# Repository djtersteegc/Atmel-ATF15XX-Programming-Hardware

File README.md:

Recently I needed to program some Atmel ATF1504AS and ATF1508AS CPLD's as part of Peter Schranz's [RVL12 emulator](https://www.5volts.ch/pages/rlv12v2/) project.  I had worked with similar Altera Max 7000 EPM7128SLC84 CPLD's that can be programmed with the readily available USB Blaster clones (~$20), but the only modern'ish programmer available for the Atmel's was Kana/Microchip's [ATDH1150USB](https://www.microchip.com/en-us/development-tool/atdh1150usb) which has risen to ~$100 over the last few years and seems to be getting harder to find in stock.  I tried various other FTDI based programmers and OpenOCD using the excellent writeup on https://www.hackup.net/2020/01/erasing-and-programming-the-atf1504-cpld/, but I couldn't get that setup to work reliably(3.3V source with 5V target?) so I ended up buying an uncased ATDH1150USB off eBay (unfortunately shipping from England to the US was more than the programmer itself), which worked great but got me motivated to do some additional work in this area.

# [ATDH1150USB 3D Printed Case](Atmel-ATDH1150USB-Case)

First I needed a case.  Simple two piece model that screws together with two M3x10mm taper head screws.

# [Atmel-ATF15XX-Programming-Adapter](Atmel-ATF15XX-Programming-Adapter)

Next I wanted to create a programming adapter than takes either a PLCC44 or PLCC84 adapter board to allow for easy used chip testing and programming. I had bought some cheap ATF1508AS's from AliExpress and a couple of them were JTAG locked so I needed a way to apply 12V to the OE1 pin to restore JTAG functionality. I had designed a similar board for [Xilinx XC9500](https://github.com/djtersteegc/xilinx-xc9500xl-programming-adapter) CPLD's, so this was a variation on that theme.

[Atmel-ATF15XX-Programming-Adapter Schematic](https://djtersteegc.github.io/Atmel-ATF15XX-Programming-Hardware/Atmel-ATF15XX-Programming-Adapter-Schematic-v1.0.pdf)

[Atmel-ATF15XX-Programming-Adapter BOM](https://djtersteegc.github.io/Atmel-ATF15XX-Programming-Hardware/Atmel-ATF15XX-Programming-Adapter-ibom-v1.0.html)

JP1 selected whetherthe ATF15xx will be powered by the (optional) onboard VRM's or directly from the supply into the DC barrel jack.

JP2 selects whether you'll see 5V or 3.3V volts at the ATF15xx.  When using the VRM's, make sure the supply voltage is a couple of volts higher, but less than the 12V being output by the boost convertor.

The bottom left locking push button controls board power, and the top right controls if +12V is routed to OE1 on the ATF15xx. When needing to execute this to reenable JTAG, make sure to apply VCC first, then 12V (top right button), program the chip, power off 12V, and then power off VCC. You may initially get a verify error on this program attempt, but once you repower the chip and try again, everything should work normally.

I designed three adapter PCB's for both normal PLCC sockets and a PLCC84 test socket.  

[PLCC-44-Socket-Adapter](PLCC-44-Socket-Adapter)	[Schematic](https://djtersteegc.github.io/Atmel-ATF15XX-Programming-Hardware/PLCC-44-Socket-Adapter-Schematic-v1.0.pdf)	[BOM](https://djtersteegc.github.io/Atmel-ATF15XX-Programming-Hardware/PLCC-44-Socket-Adapter-ibom-v1.0.html)

[PLCC-84-Socket-Adapter](PLCC-84-Socket-Adapter)	[Schematic](https://djtersteegc.github.io/Atmel-ATF15XX-Programming-Hardware/PLCC-84-Socket-Adapter-Schematic-v1.0.pdf)	[BOM](https://djtersteegc.github.io/Atmel-ATF15XX-Programming-Hardware/PLCC-84-Socket-Adapter-ibom-v1.0.html)

[PLCC-84-Test-Socket-Adapter](PLCC-84-Test-Socket-Adapter)	[Schematic](https://djtersteegc.github.io/Atmel-ATF15XX-Programming-Hardware/PLCC-84-Test-Socket-Adapter-Schematic-v1.0.pdf)	[BOM](https://djtersteegc.github.io/Atmel-ATF15XX-Programming-Hardware/PLCC-84-Test-Socket-Adapter-ibom-v1.0.html)

The PLCC84 test socket I used was this (genuine?) Yamaichi IC120-0844-303 socket without PCB that I purchased from [AliExpress](https://www.aliexpress.us/item/3256806424159192.html).  Make sure you get this model since there are other Yamaichi IC120-0844-XXX models with the "less compatible" pin pattern that won't fit.

I didn't design a PLC44 test socket to DIP44 board since these are readily available with a test socket preinstalled on [AliExpress](https://www.aliexpress.us/item/3256807303077235.html) for <$15.

Also works great for programming Max 7000's devices that share a similar pinout.

# ATMISP Compatible Programmer

I spent a bit of time reading through this [thread](https://www.forum64.de/index.php?thread/94552-atf1504as-cpld-f%C3%BCr-fe3-%C3%BCber-jtag-programmieren/) on Forum64 , and the efforts there to get various generic FTDI boards recognized by Atmel's [ATMISP](https://www.microchip.com/en-us/development-tool/atmisp) programming software.  At it's core the ATDH1150USB is an FTDI2232D with a config EEPROM to identify itself to ATMISP, level converters on the JTAG lines to support 5V and 3.3V ATF15xx chips, and some status LED's.  Here's the block diagram from the manual.

Several hours of reverse engineering and I was able to create a functional equivalent.  Went with a USB-C port since it's 2025 and dropped the JTAG-X connector to keep the board size down.

Worked great with ATMISP v7.3 on Windows 10.  Similar to the ATDH1150USB the green LED will light when connected to ATMISP, both green and red LED's when successfully executing an operation, and the red LED only when an error occurs.

Size comparison with his older brother.

I'm not going to publish the design files on this one just yet until I get rid of my initial batch of PCB's and parts, so if you are in the US and interested in an assembled and tested programmer as pictured above for half the cost of the official ATDH1150USB, drop me a line.  Should also have them up on [Tindie](https://www.tindie.com/stores/tersteeg/) in a bit.

Shield: [![CC BY-NC-SA 4.0][cc-by-nc-sa-shield]][cc-by-nc-sa]

This work is licensed under a
[Creative Commons Attribution-NonCommercial-ShareAlike 4.0 International License][cc-by-nc-sa].

[![CC BY-NC-SA 4.0][cc-by-nc-sa-image]][cc-by-nc-sa]

[cc-by-nc-sa]: http://creativecommons.org/licenses/by-nc-sa/4.0/
[cc-by-nc-sa-image]: https://licensebuttons.net/l/by-nc-sa/4.0/88x31.png
[cc-by-nc-sa-shield]: https://img.shields.io/badge/License-CC%20BY--NC--SA%204.0-lightgrey.svg

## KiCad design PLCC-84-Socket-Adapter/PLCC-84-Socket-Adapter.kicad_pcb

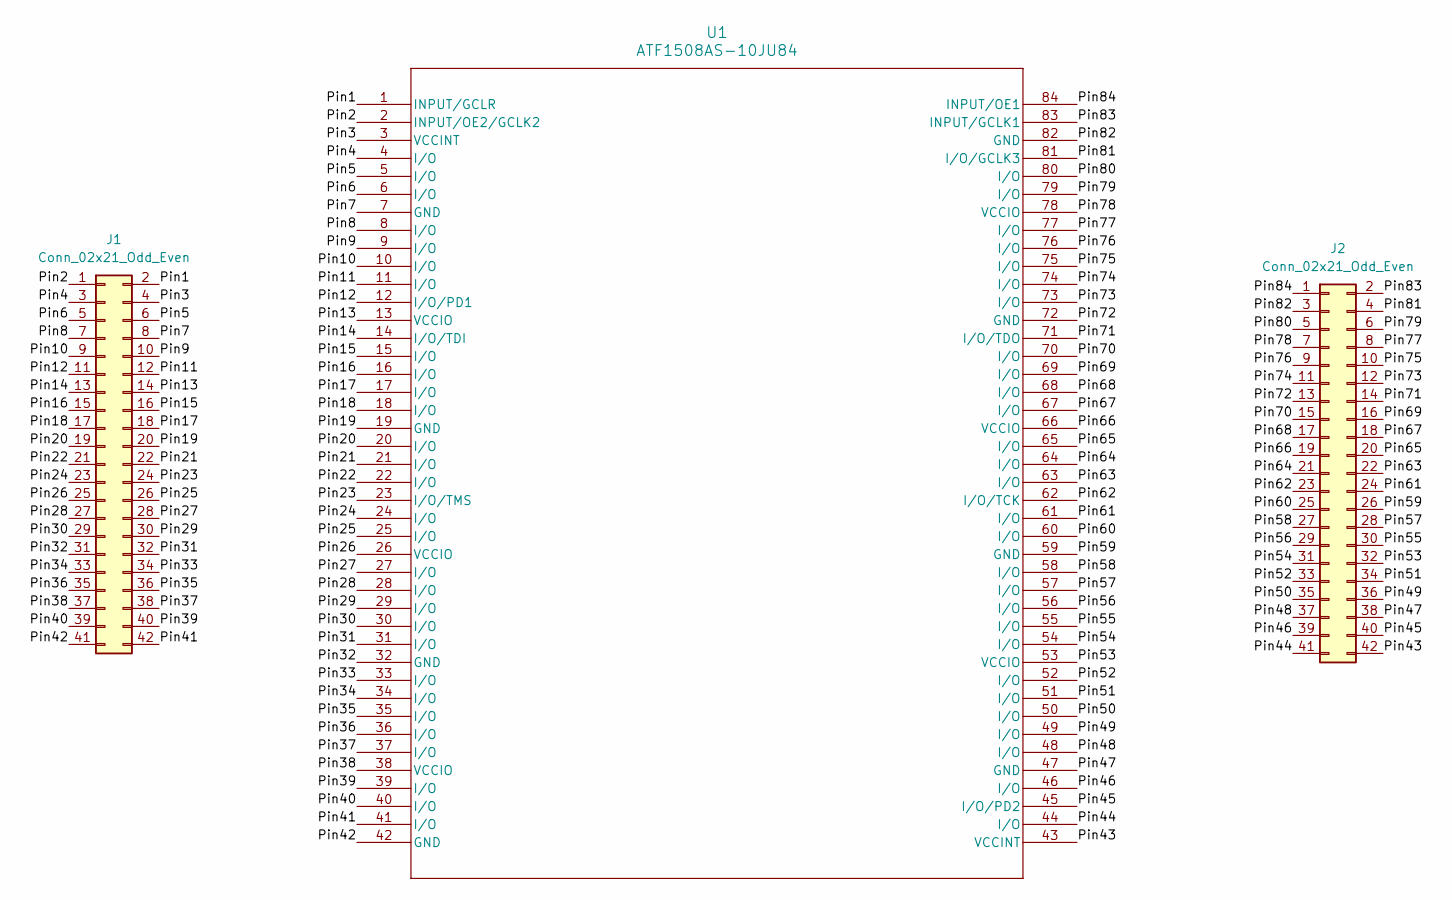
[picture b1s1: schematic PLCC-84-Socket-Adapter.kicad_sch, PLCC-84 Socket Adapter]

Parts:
J1, J2: Conn_02x21_Odd_Even; PinHeader_2x21_P2.54mm_Vertical
U1: ATF1508AS-10JU84; PLCC-84_THT-Socket

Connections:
/Pin1: J1.2, U1.1 (INPUT/GCLR)
/Pin2: J1.1, U1.2 (INPUT/OE2/GCLK2)
/Pin3: J1.4, U1.3 (VCCINT)
/Pin4: J1.3, U1.4 (I/O)
/Pin5: J1.6, U1.5 (I/O)
/Pin6: J1.5, U1.6 (I/O)
/Pin7: J1.8, U1.7 (GND)
/Pin8: J1.7, U1.8 (I/O)
/Pin9: J1.10, U1.9 (I/O)
/Pin10: J1.9, U1.10 (I/O)
/Pin11: J1.12, U1.11 (I/O)
/Pin12: J1.11, U1.12 (I/O/PD1)
/Pin13: J1.14, U1.13 (VCCIO)
/Pin14: J1.13, U1.14 (I/O/TDI)
/Pin15: J1.16, U1.15 (I/O)
/Pin16: J1.15, U1.16 (I/O)
/Pin17: J1.18, U1.17 (I/O)
/Pin18: J1.17, U1.18 (I/O)
/Pin19: J1.20, U1.19 (GND)
/Pin20: J1.19, U1.20 (I/O)
/Pin21: J1.22, U1.21 (I/O)
/Pin22: J1.21, U1.22 (I/O)
/Pin23: J1.24, U1.23 (I/O/TMS)
/Pin24: J1.23, U1.24 (I/O)
/Pin25: J1.26, U1.25 (I/O)
/Pin26: J1.25, U1.26 (VCCIO)
/Pin27: J1.28, U1.27 (I/O)
/Pin28: J1.27, U1.28 (I/O)
/Pin29: J1.30, U1.29 (I/O)
/Pin30: J1.29, U1.30 (I/O)
/Pin31: J1.32, U1.31 (I/O)
/Pin32: J1.31, U1.32 (GND)
/Pin33: J1.34, U1.33 (I/O)
/Pin34: J1.33, U1.34 (I/O)
/Pin35: J1.36, U1.35 (I/O)
/Pin36: J1.35, U1.36 (I/O)
/Pin37: J1.38, U1.37 (I/O)
/Pin38: J1.37, U1.38 (VCCIO)
/Pin39: J1.40, U1.39 (I/O)
/Pin40: J1.39, U1.40 (I/O)
/Pin41: J1.42, U1.41 (I/O)
/Pin42: J1.41, U1.42 (GND)
/Pin43: J2.42, U1.43 (VCCINT)
/Pin44: J2.41, U1.44 (I/O)
/Pin45: J2.40, U1.45 (I/O/PD2)
/Pin46: J2.39, U1.46 (I/O)
/Pin47: J2.38, U1.47 (GND)
/Pin48: J2.37, U1.48 (I/O)
/Pin49: J2.36, U1.49 (I/O)
/Pin50: J2.35, U1.50 (I/O)
/Pin51: J2.34, U1.51 (I/O)
/Pin52: J2.33, U1.52 (I/O)
/Pin53: J2.32, U1.53 (VCCIO)
/Pin54: J2.31, U1.54 (I/O)
/Pin55: J2.30, U1.55 (I/O)
/Pin56: J2.29, U1.56 (I/O)
/Pin57: J2.28, U1.57 (I/O)
/Pin58: J2.27, U1.58 (I/O)
/Pin59: J2.26, U1.59 (GND)
/Pin60: J2.25, U1.60 (I/O)
/Pin61: J2.24, U1.61 (I/O)
/Pin62: J2.23, U1.62 (I/O/TCK)
/Pin63: J2.22, U1.63 (I/O)
/Pin64: J2.21, U1.64 (I/O)
/Pin65: J2.20, U1.65 (I/O)
/Pin66: J2.19, U1.66 (VCCIO)
/Pin67: J2.18, U1.67 (I/O)
/Pin68: J2.17, U1.68 (I/O)
/Pin69: J2.16, U1.69 (I/O)
/Pin70: J2.15, U1.70 (I/O)
/Pin71: J2.14, U1.71 (I/O/TDO)
/Pin72: J2.13, U1.72 (GND)
/Pin73: J2.12, U1.73 (I/O)
/Pin74: J2.11, U1.74 (I/O)
/Pin75: J2.10, U1.75 (I/O)
/Pin76: J2.9, U1.76 (I/O)
/Pin77: J2.8, U1.77 (I/O)
/Pin78: J2.7, U1.78 (VCCIO)
/Pin79: J2.6, U1.79 (I/O)
/Pin80: J2.5, U1.80 (I/O)
/Pin81: J2.4, U1.81 (I/O/GCLK3)
/Pin82: J2.3, U1.82 (GND)
/Pin83: J2.2, U1.83 (INPUT/GCLK1)
/Pin84: J2.1, U1.84 (INPUT/OE1)

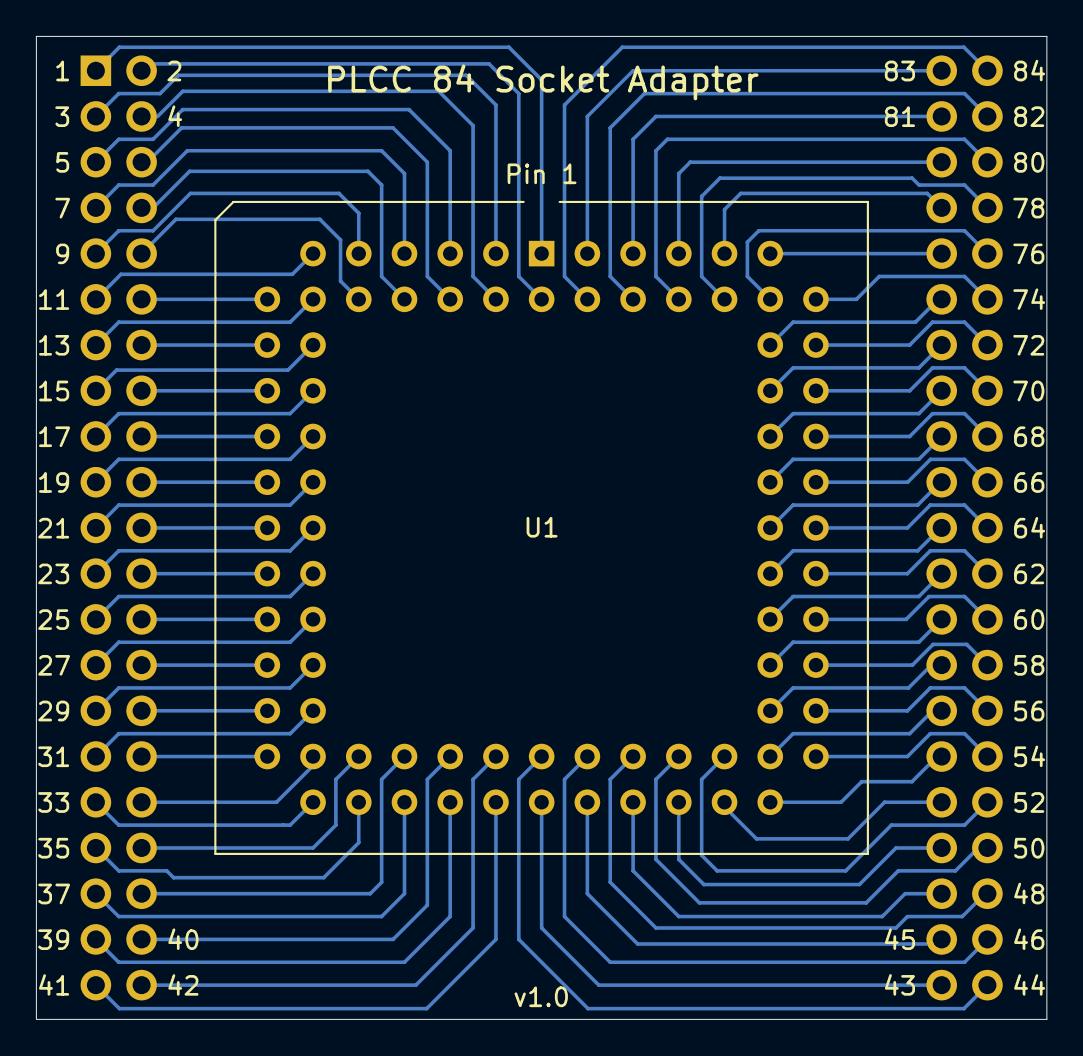
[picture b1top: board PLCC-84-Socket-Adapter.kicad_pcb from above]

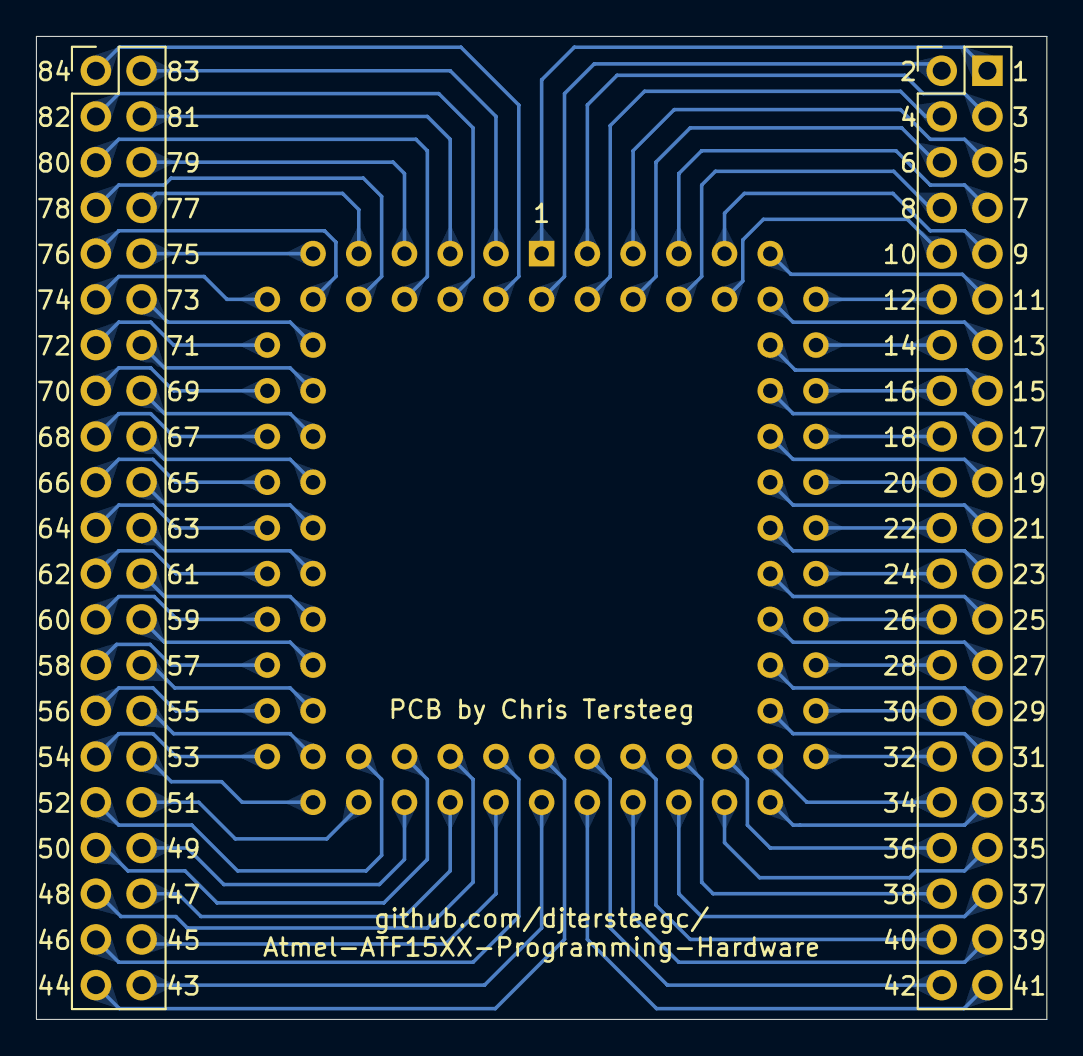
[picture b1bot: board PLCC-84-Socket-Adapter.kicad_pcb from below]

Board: 2 copper layers, 56.1 x 54.6 mm, 3 parts (2 on the bottom side), 84 nets.

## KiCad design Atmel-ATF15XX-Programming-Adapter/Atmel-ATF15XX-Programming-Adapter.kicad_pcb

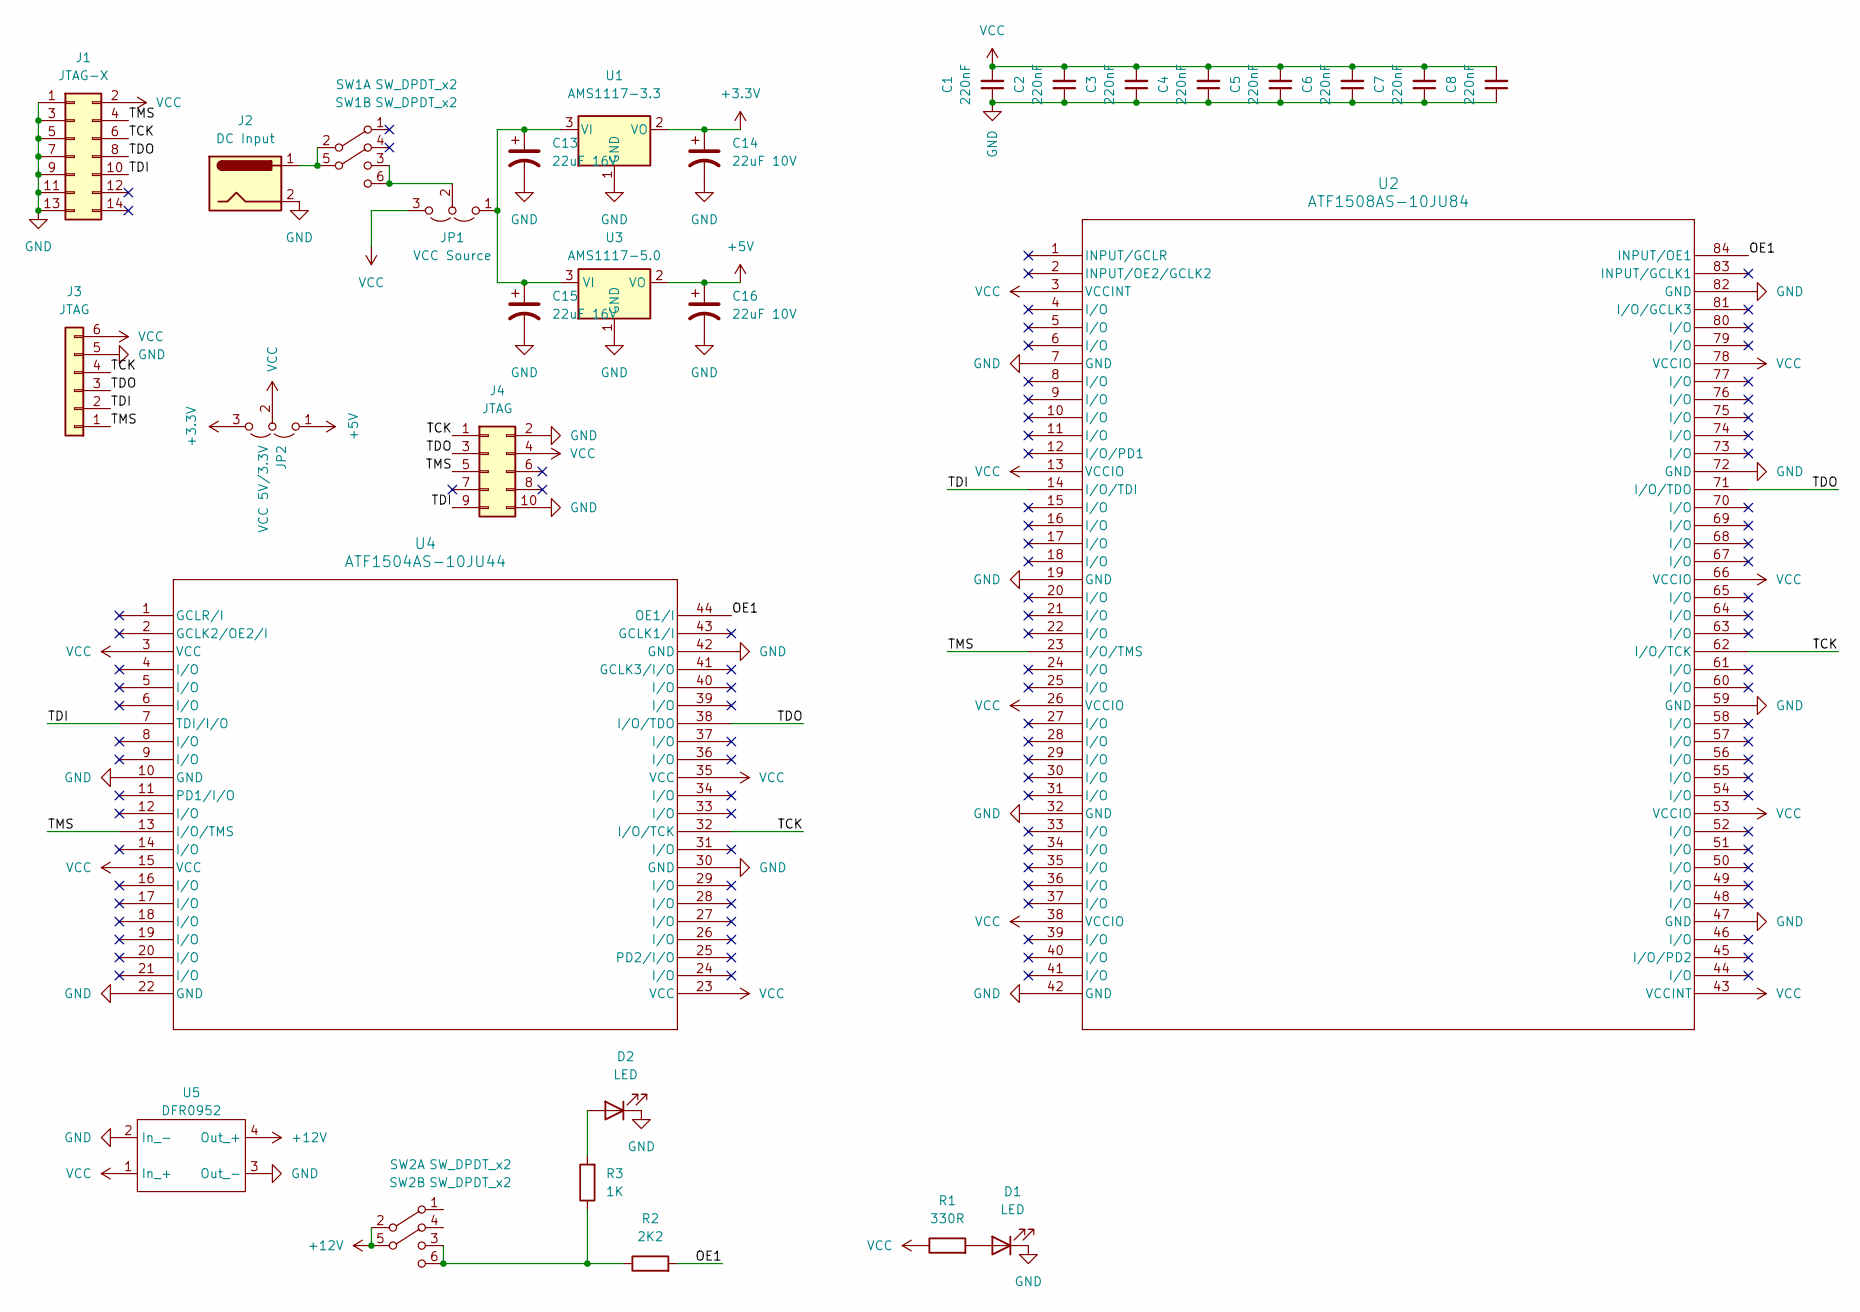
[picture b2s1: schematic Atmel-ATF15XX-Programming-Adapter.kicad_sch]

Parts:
C1, C2, C3, C4, C5, C6, C7, C8: 220nF; C_Disc_D4.7mm_W2.5mm_P5.00mm
C13, C15: 22uF 16V; CP_EIA-3528-12_Kemet-T_Pad1.50x2.35mm_HandSolder
C14, C16: 22uF 10V; CP_EIA-3528-12_Kemet-T_Pad1.50x2.35mm_HandSolder
D1, D2: LED; LED_D3.0mm
J1: JTAG-X; IDC-Header_2x07_P2.00mm_Vertical
J2: DC Input; BarrelJack_Horizontal
J3: JTAG; PinHeader_1x06_P2.54mm_Horizontal
J4: JTAG; IDC-Header_2x05_P2.54mm_Vertical
JP1: VCC Source; PinHeader_1x03_P2.54mm_Vertical
JP2: VCC 5V/3.3V; PinHeader_1x03_P2.54mm_Vertical
R1: 330R; R_Axial_DIN0207_L6.3mm_D2.5mm_P7.62mm_Horizontal
R2: 2K2; R_Axial_DIN0207_L6.3mm_D2.5mm_P7.62mm_Horizontal
R3: 1K; R_Axial_DIN0207_L6.3mm_D2.5mm_P7.62mm_Horizontal
SW1, SW2: SW_DPDT_x2; KFC8.5x8.5 DPDT Push Switch
U1: AMS1117-3.3; SOT-223-3_TabPin2
U2: ATF1508AS-10JU84; PLCC84 to Dual DIP84
U3: AMS1117-5.0; SOT-223-3_TabPin2
U4: ATF1504AS-10JU44; PLCC44-QFP44 to DIP44
U5: DFR0952; DFR0952 Mini DC-DC Boost Convertor

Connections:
+3.3V: C14.1, JP2.3 (B), U1.2 (VO)
+5V: C16.1, JP2.1 (A), U3.2 (VO)
+12V: SW2.2 (B), SW2.5 (B), U5.4 (Out_+)
/OE1: R2.2, U2.84 (INPUT/OE1), U4.44 (OE1/I)
/TCK: J1.6, J3.4, J4.1, U2.62 (I/O/TCK), U4.32 (I/O/TCK)
/TDI: J1.10, J3.2, J4.9, U2.14 (I/O/TDI), U4.7 (TDI/I/O)
/TDO: J1.8, J3.3, J4.3, U2.71 (I/O/TDO), U4.38 (I/O/TDO)
/TMS: J1.4, J3.1, J4.5, U2.23 (I/O/TMS), U4.13 (I/O/TMS)
GND: C1.1, C2.1, C3.1, C4.1, C5.1, C6.1, C7.1, C8.1, C13.2, C14.2, C15.2, C16.2, D1.1 (K), D2.1 (K), J1.1, J1.3, J1.5, J1.7, J1.9, J1.11, J1.13, J2.2, J3.5, J4.2, J4.10, U1.1 (GND), U2.7 (GND), U2.19 (GND), U2.32 (GND), U2.42 (GND), U2.47 (GND), U2.59 (GND), U2.72 (GND), U2.82 (GND), U3.1 (GND), U4.10 (GND), U4.22 (GND), U4.30 (GND), U4.42 (GND), U5.2 (In_-), U5.3 (Out_-)
unnamed: D1.2 (A), R1.2
unnamed: D2.2 (A), R3.2
unnamed: C13.1, C15.1, JP1.1 (A), U1.3 (VI), U3.3 (VI)
unnamed: JP1.2 (C), SW1.3 (C), SW1.6 (C)
unnamed: J2.1, SW1.2 (B), SW1.5 (B)
unnamed: R2.1, R3.1, SW2.3 (C), SW2.6 (C)
VCC: C1.2, C2.2, C3.2, C4.2, C5.2, C6.2, C7.2, C8.2, J1.2, J3.6, J4.4, JP1.3 (B), JP2.2 (C), R1.1, U2.3 (VCCINT), U2.13 (VCCIO), U2.26 (VCCIO), U2.38 (VCCIO), U2.43 (VCCINT), U2.53 (VCCIO), U2.66 (VCCIO), U2.78 (VCCIO), U4.3 (VCC), U4.15 (VCC), U4.23 (VCC), U4.35 (VCC), U5.1 (In_+)

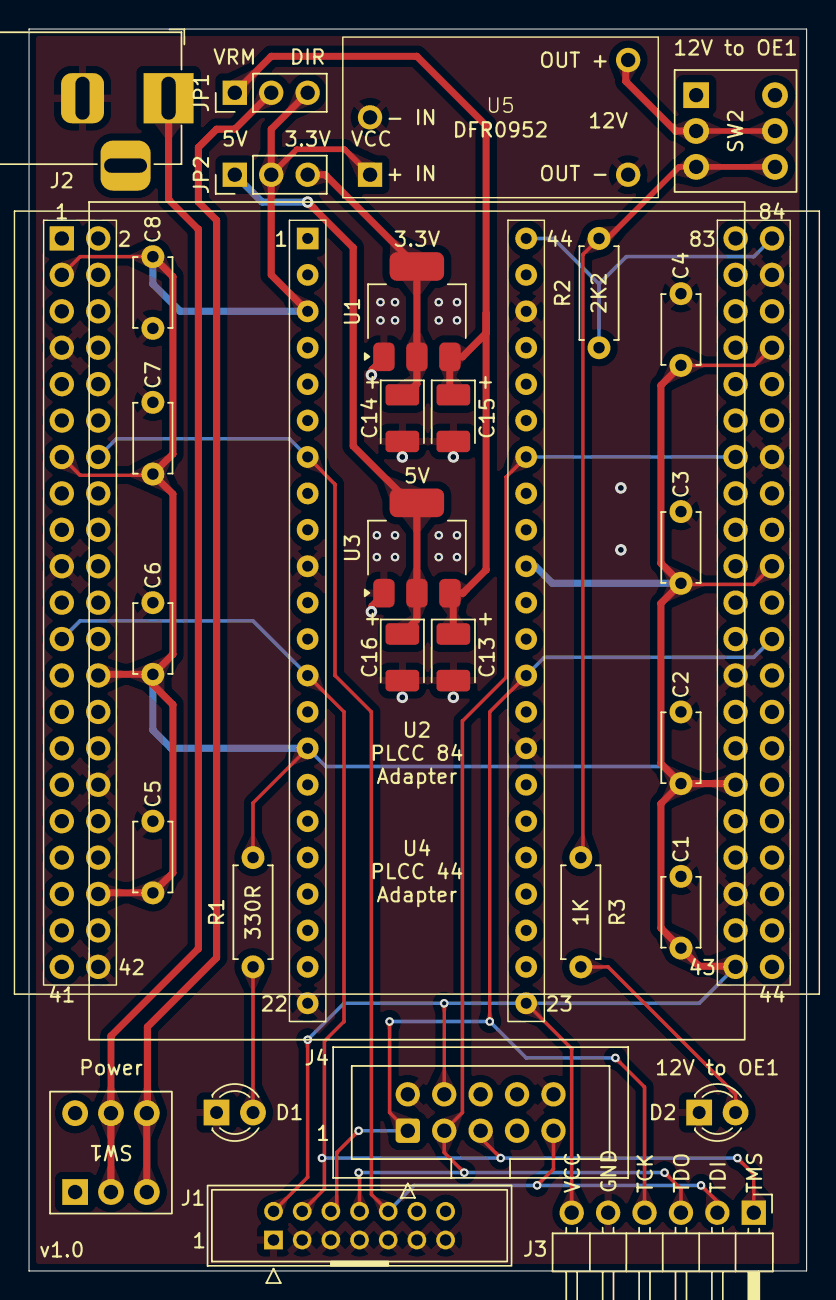
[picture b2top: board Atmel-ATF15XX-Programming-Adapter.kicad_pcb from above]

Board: 2 copper layers, 54.2 x 86.6 mm, 30 parts (0 on the bottom side), 16 nets.

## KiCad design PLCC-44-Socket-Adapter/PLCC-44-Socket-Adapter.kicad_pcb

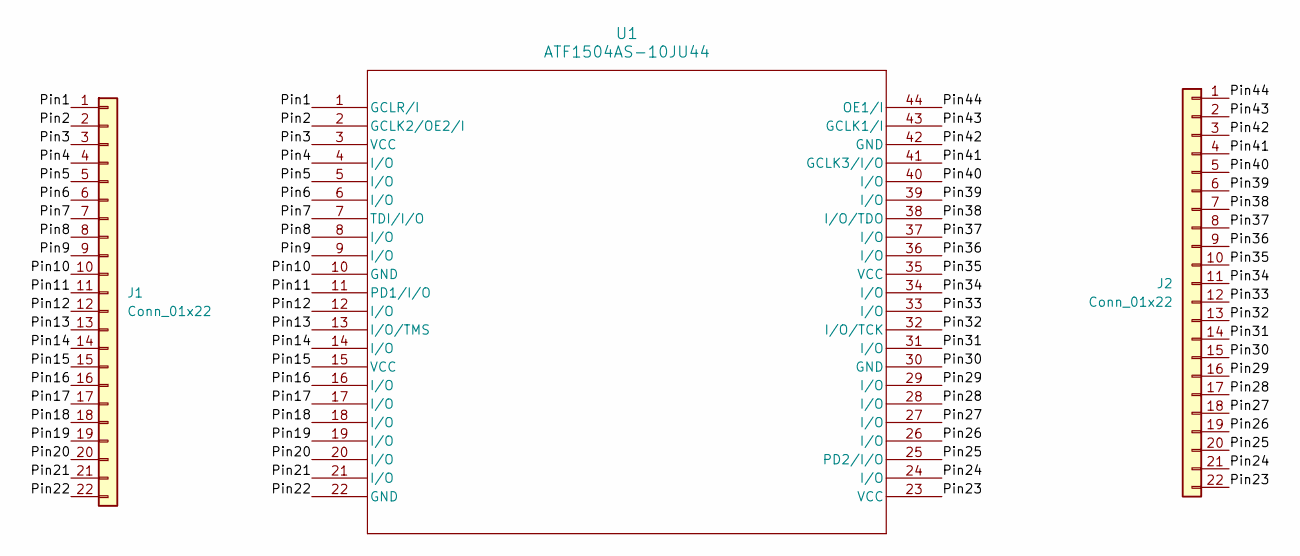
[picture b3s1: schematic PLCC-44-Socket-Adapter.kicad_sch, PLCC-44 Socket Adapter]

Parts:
J1, J2: Conn_01x22; PinHeader_1x22_P2.54mm_Vertical
U1: ATF1504AS-10JU44; PLCC-44_THT-Socket

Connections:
/Pin1: J1.1, U1.1 (GCLR/I)
/Pin2: J1.2, U1.2 (GCLK2/OE2/I)
/Pin3: J1.3, U1.3 (VCC)
/Pin4: J1.4, U1.4 (I/O)
/Pin5: J1.5, U1.5 (I/O)
/Pin6: J1.6, U1.6 (I/O)
/Pin7: J1.7, U1.7 (TDI/I/O)
/Pin8: J1.8, U1.8 (I/O)
/Pin9: J1.9, U1.9 (I/O)
/Pin10: J1.10, U1.10 (GND)
/Pin11: J1.11, U1.11 (PD1/I/O)
/Pin12: J1.12, U1.12 (I/O)
/Pin13: J1.13, U1.13 (I/O/TMS)
/Pin14: J1.14, U1.14 (I/O)
/Pin15: J1.15, U1.15 (VCC)
/Pin16: J1.16, U1.16 (I/O)
/Pin17: J1.17, U1.17 (I/O)
/Pin18: J1.18, U1.18 (I/O)
/Pin19: J1.19, U1.19 (I/O)
/Pin20: J1.20, U1.20 (I/O)
/Pin21: J1.21, U1.21 (I/O)
/Pin22: J1.22, U1.22 (GND)
/Pin23: J2.22, U1.23 (VCC)
/Pin24: J2.21, U1.24 (I/O)
/Pin25: J2.20, U1.25 (PD2/I/O)
/Pin26: J2.19, U1.26 (I/O)
/Pin27: J2.18, U1.27 (I/O)
/Pin28: J2.17, U1.28 (I/O)
/Pin29: J2.16, U1.29 (I/O)
/Pin30: J2.15, U1.30 (GND)
/Pin31: J2.14, U1.31 (I/O)
/Pin32: J2.13, U1.32 (I/O/TCK)
/Pin33: J2.12, U1.33 (I/O)
/Pin34: J2.11, U1.34 (I/O)
/Pin35: J2.10, U1.35 (VCC)
/Pin36: J2.9, U1.36 (I/O)
/Pin37: J2.8, U1.37 (I/O)
/Pin38: J2.7, U1.38 (I/O/TDO)
/Pin39: J2.6, U1.39 (I/O)
/Pin40: J2.5, U1.40 (I/O)
/Pin41: J2.4, U1.41 (GCLK3/I/O)
/Pin42: J2.3, U1.42 (GND)
/Pin43: J2.2, U1.43 (GCLK1/I)
/Pin44: J2.1, U1.44 (OE1/I)

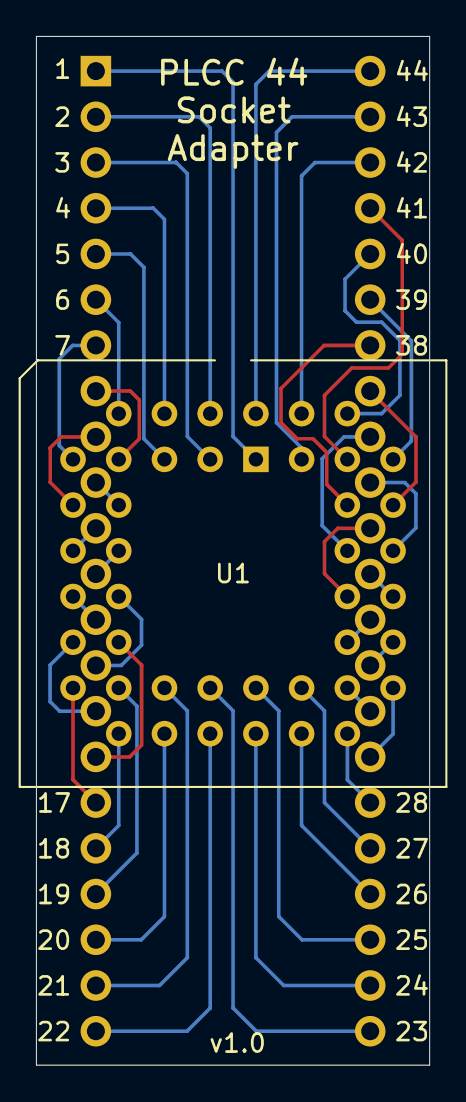
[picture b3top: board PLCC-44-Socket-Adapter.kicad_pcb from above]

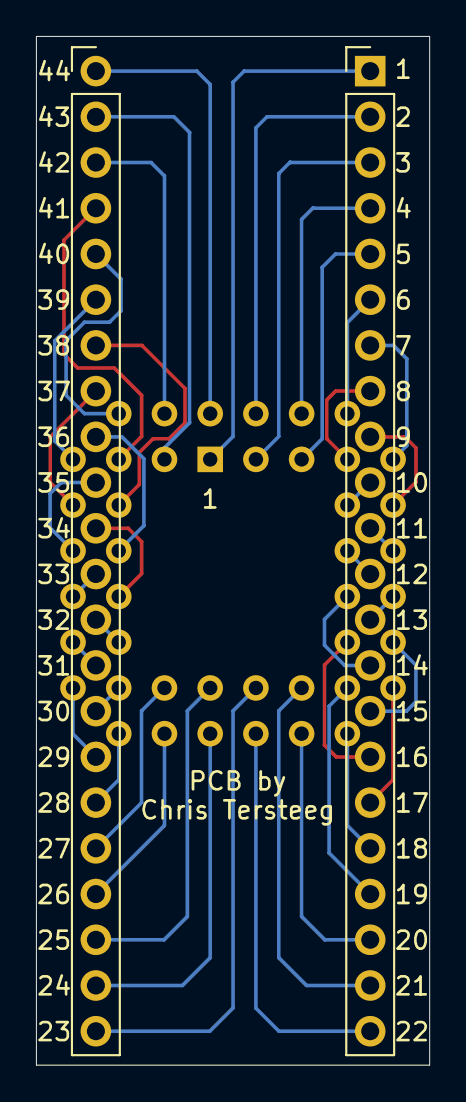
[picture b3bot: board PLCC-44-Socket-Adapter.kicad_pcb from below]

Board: 2 copper layers, 21.8 x 57.1 mm, 3 parts (2 on the bottom side), 44 nets.

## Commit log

2025-03-14 Update docs
2025-03-14 Update LICENSE
2025-03-14 Fix README
